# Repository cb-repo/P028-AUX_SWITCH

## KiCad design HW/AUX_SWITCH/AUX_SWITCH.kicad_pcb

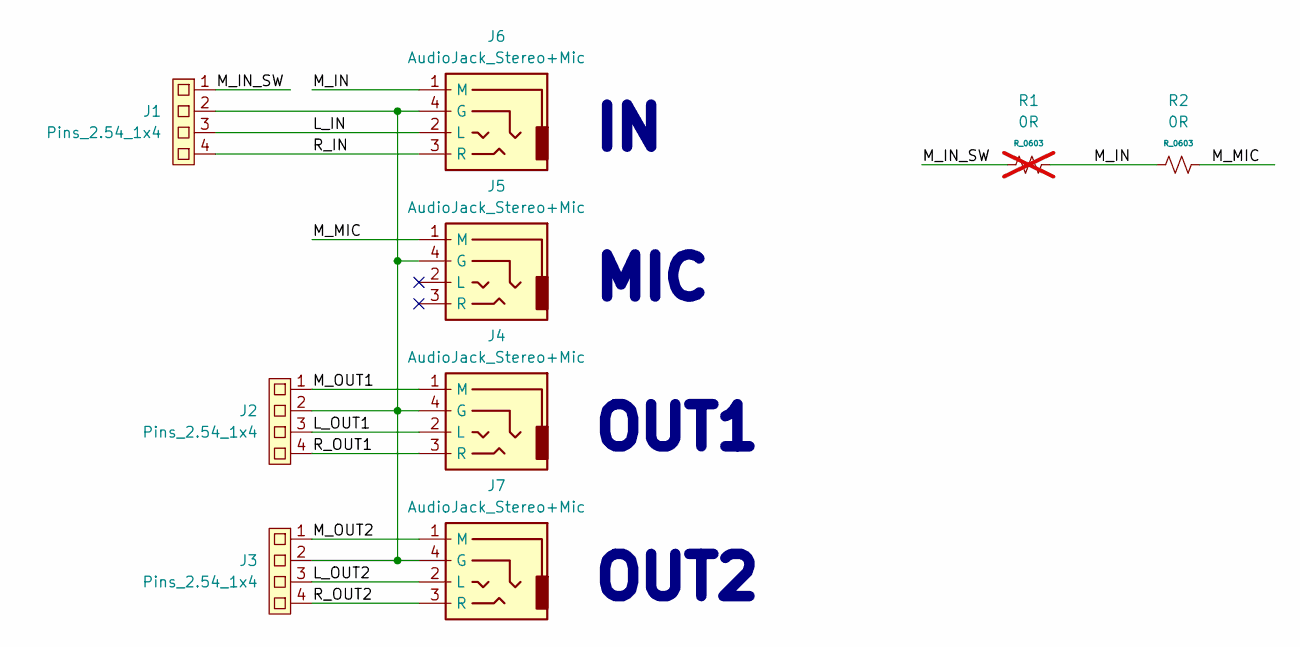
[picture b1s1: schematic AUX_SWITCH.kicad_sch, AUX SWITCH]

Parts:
J1, J2, J3: Pins_2.54_1x4; Pins-2.54-1x4
J4, J5, J6, J7: AudioJack_Stereo+Mic; AudioJack_STX-35061-4T
R1: 0R; R_0603; not fitted
R2: 0R; R_0603

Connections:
/L_IN: J1.3, J6.2 (L)
/L_OUT1: J2.3, J4.2 (L)
/L_OUT2: J3.3, J7.2 (L)
/M_IN: J6.1 (M), R1.2, R2.1
/M_IN_SW: J1.1, R1.1
/M_MIC: J5.1 (M), R2.2
/M_OUT1: J2.1, J4.1 (M)
/M_OUT2: J3.1, J7.1 (M)
/R_IN: J1.4, J6.3 (R)
/R_OUT1: J2.4, J4.3 (R)
/R_OUT2: J3.4, J7.3 (R)
unnamed: J1.2, J2.2, J3.2, J4.4 (G), J5.4 (G), J6.4 (G), J7.4 (G)

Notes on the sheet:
OUT1
OUT2
MIC

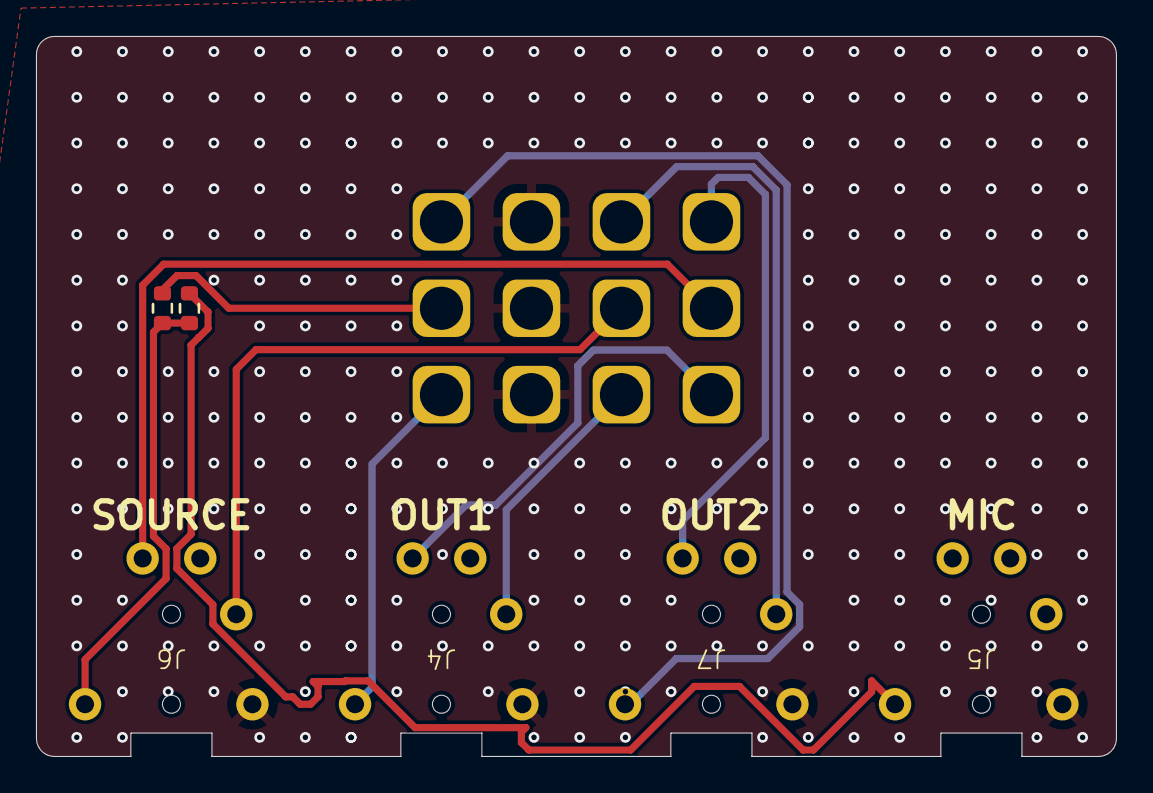
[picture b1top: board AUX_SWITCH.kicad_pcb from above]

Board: 2 copper layers, 60.0 x 40.0 mm, 9 parts (0 on the bottom side), 12 nets.

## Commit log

2023-08-06 Start and Finish Aux Switch PCB
